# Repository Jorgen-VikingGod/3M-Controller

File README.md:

# 3M-Controller
3M-Controller = Multi Modular MIDI Controller

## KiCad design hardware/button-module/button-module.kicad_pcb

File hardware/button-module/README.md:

# BOM (for 1 board)
|QUANTITY|TYPE|DESCRIPTION|PACKAGE|Reference|
|--------|----|-----------|-------|---------|
|1|Microcontroller|ATXMEGA32A4U-AU|TQFP-44|U1|
|3|LevelShifter|74HCT245PW,118|TSSOP-20|U2, U3, U4|
|1|Zener Diode|MMSZ4684-TP 3.3V|SOD-123|D21|
|1|LDO|LD1117S33TR 3.3V|SOT-223|U5|
|20|Diode|1N4148W|SOD-123|D1 - D16|
|2|Resistor|220 Ohm|SMD-0805|R1, R2|
|1|Resistor|4.7 kOhm|SMD-0805|R5|
|1|Resistor|100 Ohm|SMD-0805|R3|
|7|Capacitor|6.3V 100 nF|SMD-0805|C1 - C7|

# BOM (for 10 boards, [arrow.com](https://www.arrow.com))
|PART|MANUFACTURER|QUANTITY|PRICE|PRICE TOTAL|DESCRIPTION|DETAILS|
|----|------------|--------|-----|-----------|-----------|-------|
|ATXMEGA32A4U-AU|Microchip Technology|10|2,4737|24,737|MCU 8-bit/16-bit XMEGA AVR RISC 32KB Flash 1.8V/2.5V/3.3V 44-Pin TQFP|https://www.arrow.com/en/products/atxmega32a4u-au/microchip-technology|
|74HCT245PW,118|Nexperia|30|0,1985|5,955|Bus XCVR Single 8-CH 3-ST 20-Pin TSSOP T/R|https://www.arrow.com/products/74hct245pw118/nexperia|
|MMSZ4684-TP|Micro Commercial Components|10|0,0708|0,708|Diode Zener Single 3.3V 5% 500mW 2-Pin SOD-123 T/R|https://www.arrow.com/products/mmsz4684-tp/micro-commercial-components|
|LD1117S33TR|STMicroelectronics|10|0,1713|1,713|LDO Regulator Pos 3.3V 1.3A 4-Pin(3+Tab) SOT-223 T/R|https://www.arrow.com/products/ld1117s33tr/stmicroelectronics|
|1N4148W|Good-Ark Semiconductor|200|0,0075|1,5|Diode Switching 75V 0.15A 2-Pin SOD-123|https://www.arrow.com/products/1n4148w/good-ark-semiconductor|
|NRC10J221TRF|NIC Components|20|0,0159|0,318|Res Thick Film 0805 220 Ohm 5% 0.125W(1/8W) ±200ppm/°C Pad SMD T/R|https://www.arrow.com/products/nrc10j221trf/nic-components|
|NRC10J101TRF|NIC Components|10|0,0141|0,141|Res Thick Film 0805 100 Ohm 5% 0.125W(1/8W) ±200ppm/°C Pad SMD T/R|https://www.arrow.com/products/nrc10j101trf/nic-components|
|RC0805JR-134K7L|Yageo|10|0,0175|0,175|Res Thick Film 0805 4.7K Ohm 5% 0.125W(1/8W) ±100ppm/°C Epoxy Pad SMD T/R|https://www.arrow.com/products/rc0805jr-134k7l/yageo|
|C0805C104K9RACTU|KEMET Corporation|70|0.0759|2.277|Cap Ceramic 0.1uF 6.3V X7R 10% Pad SMD 0805 125°C T/R|https://www.arrow.com/en/products/c0805c104k9ractu/kemet-corporation|

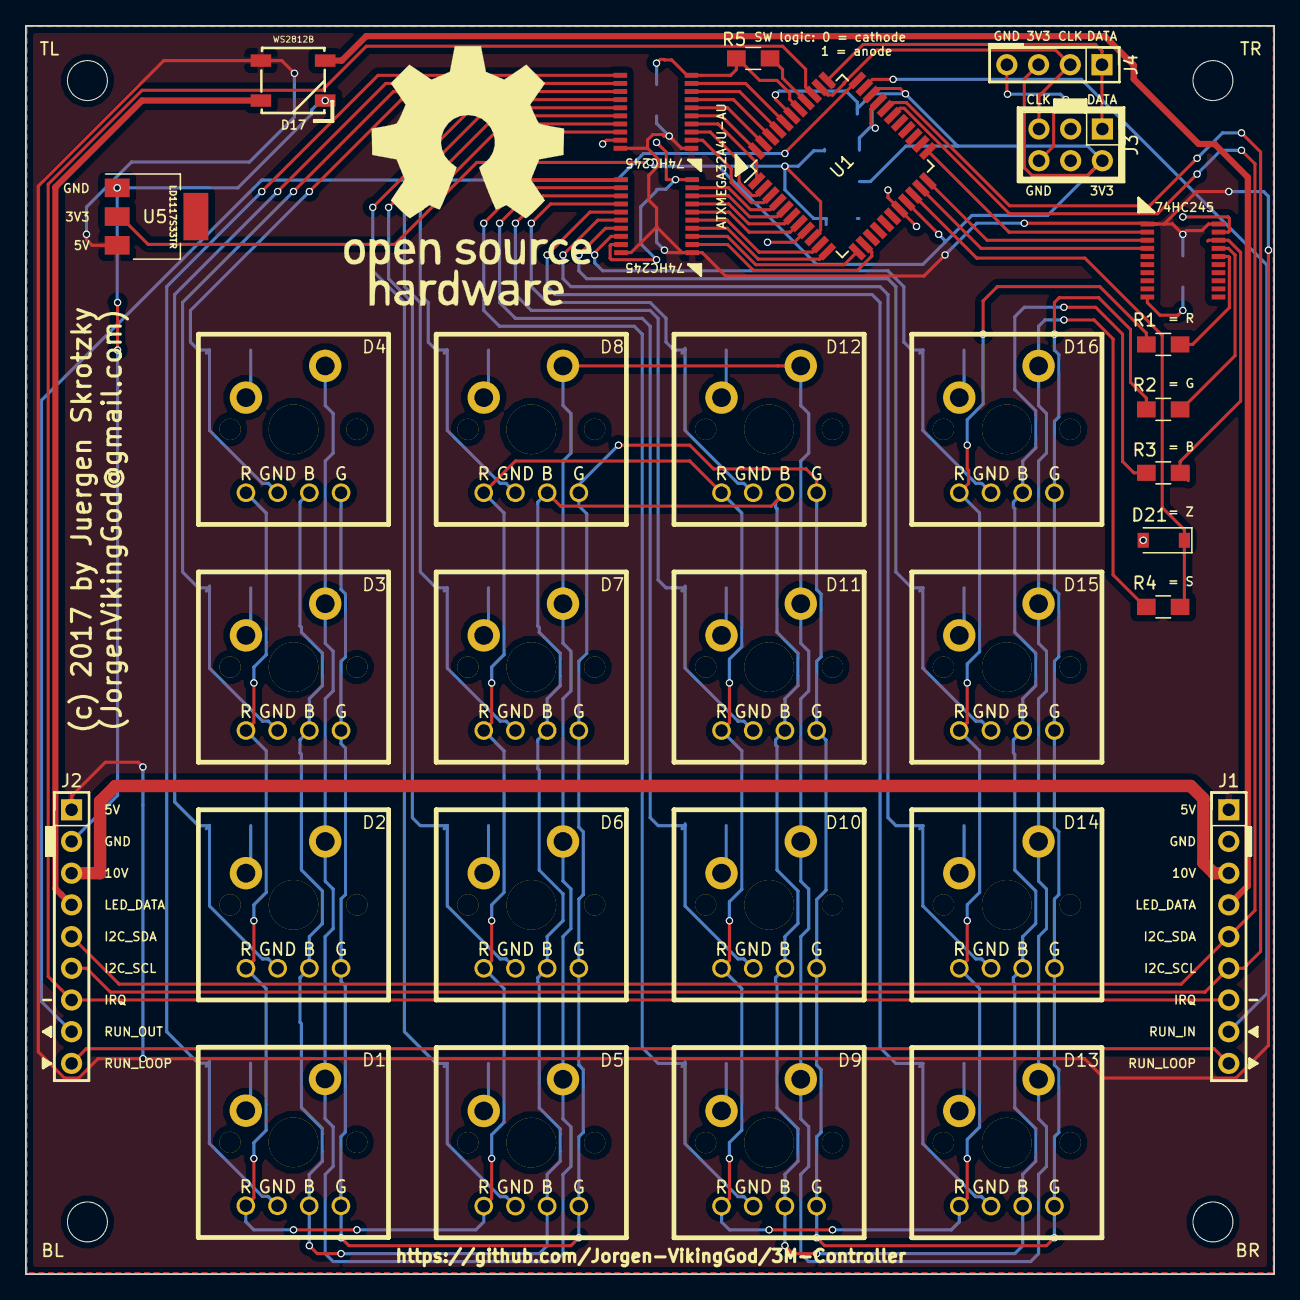
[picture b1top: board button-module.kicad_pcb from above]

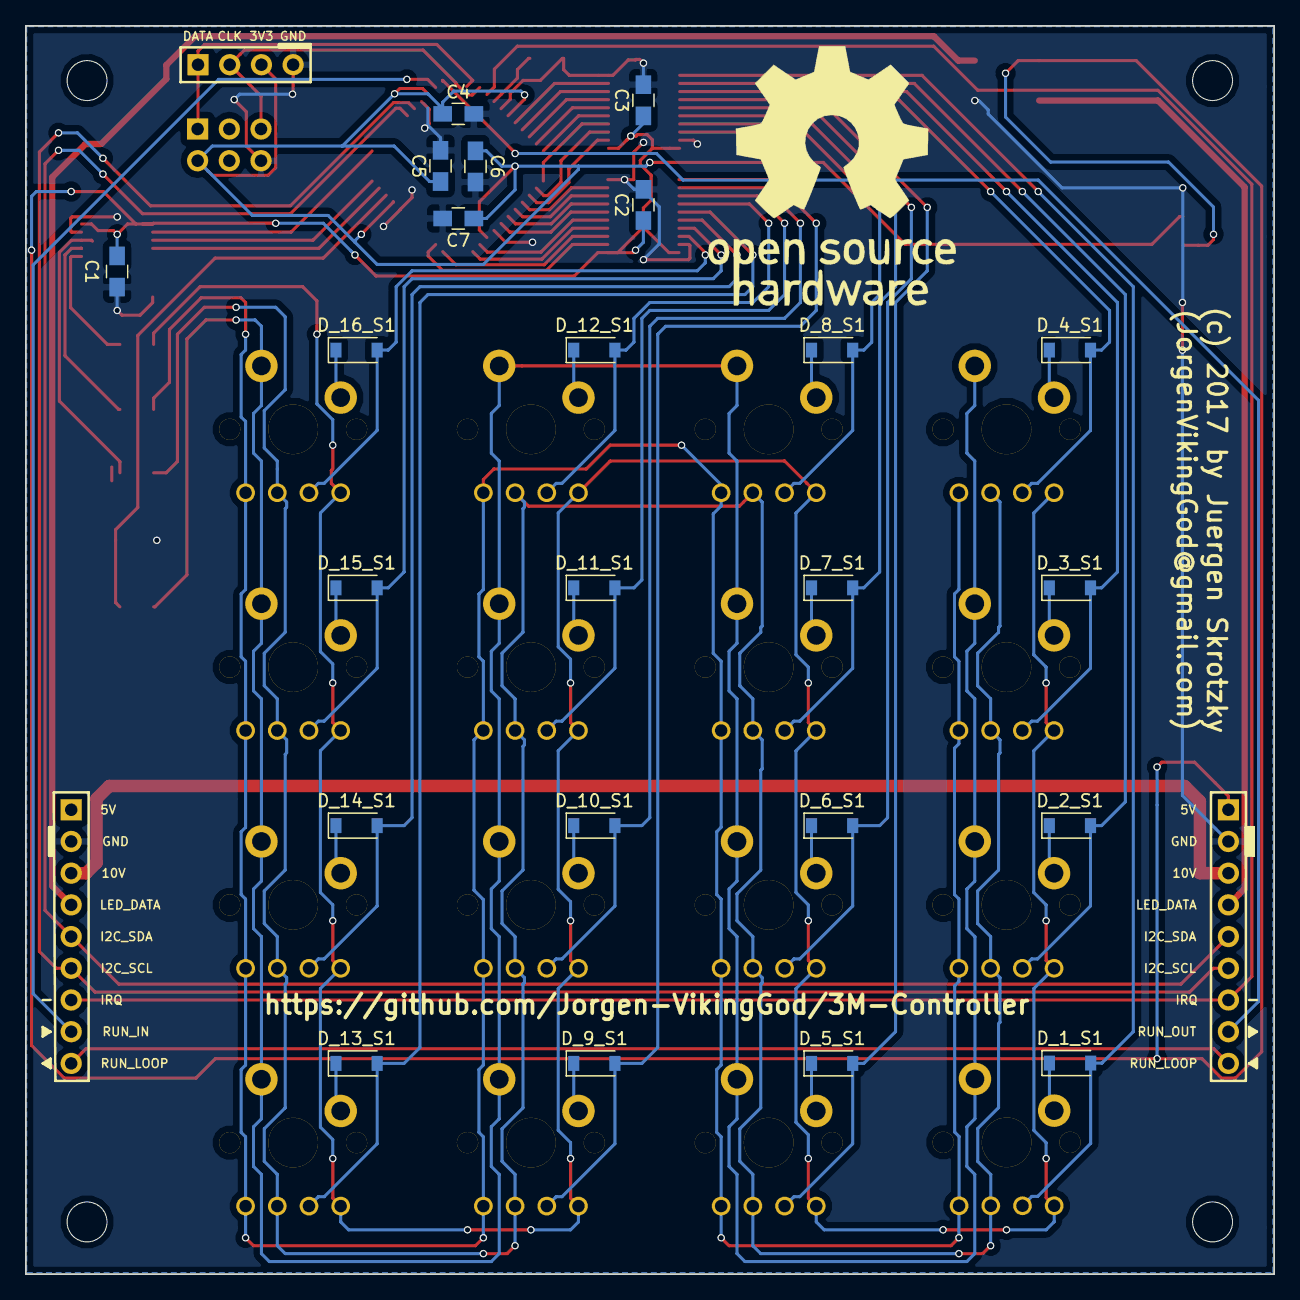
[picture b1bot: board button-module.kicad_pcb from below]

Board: 2 copper layers, 100.0 x 100.0 mm, 75 parts (23 on the bottom side), 74 nets.

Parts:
BL: MountingHole_3.2mm_M3
BR: MountingHole_3.2mm_M3
C1, C2, C3, C4, C5, C6, C7: 100n; C_0805_HandSoldering
D1: LED1; RGB
D2: LED2; RGB
D3: LED3; RGB
D4: LED4; RGB
D5: LED5; RGB
D6: LED6; RGB
D7: LED7; RGB
D8: LED8; RGB
D9: LED9; RGB
D10: LED10; RGB
D11: LED11; RGB
D12: LED12; RGB
D13: LED13; RGB
D14: LED14; RGB
D15: LED15; RGB
D16: LED16; RGB
D17: WS2812B
D21: D_Zener; D_SOD-123
D_1_S1, D_2_S1, D_3_S1, D_4_S1, D_5_S1, D_6_S1, D_7_S1, D_8_S1, D_9_S1, D_10_S1, D_11_S1, D_12_S1, D_13_S1, D_14_S1, D_15_S1, D_16_S1: D; D_SOD-123
J1, J2: CONN_01X09; Pin_Header_Straight_1x09_Pitch2.54mm
J3: CONN_02X03; Pin_Header_Straight_2x03_Pitch2.54mm
J4: CONN_01X04; Pin_Header_Straight_1x04_Pitch2.54mm
R1, R2, R3: 4K; R_0805_HandSoldering
R4, R5: R; R_0805_HandSoldering
SW1, SW2, SW3, SW4, SW5, SW6, SW7, SW8, SW9, SW10, SW11, SW12, SW13, SW14, SW15, SW16: SW_PUSH; MX1A
TL: MountingHole_3.2mm_M3
TR: MountingHole_3.2mm_M3
U1: ATXMEGA32A4U-AU; TQFP-44_10x10mm_Pitch0.8mm
U2, U3, U4: 74HC245; TSSOP20
U5: LD1117S33TR; SOT-223

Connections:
+3V3: C4.1, C5.1, C6.1, C7.1, J3.2, J4.3, U1.9, U1.19, U1.31, U1.39, U5.2
+12V: J1.3, J2.3
/C_1_R: R1.1, U4.16
/C_2_R: R2.1, U4.17
/C_3_R: R3.1, U4.18
COLOR_1_3V3: U1.21, U4.4
COLOR_1_5V: D1.2, D2.2, D3.2, D4.2, D5.2, D6.2, D7.2, D8.2, D9.2, D10.2, D11.2, D12.2, D13.2, D14.2, D15.2, D16.2, R1.2
COLOR_2_3V3: U1.22, U4.3
COLOR_2_5V: D1.3, D2.3, D3.3, D4.3, D5.3, D6.3, D7.3, D8.3, D9.3, D10.3, D11.3, D12.3, D13.3, D14.3, D15.3, D16.3, R2.2
COLOR_3_3V3: U1.23, U4.2
COLOR_3_5V: D1.4, D2.4, D3.4, D4.4, D5.4, D6.4, D7.4, D8.4, D9.4, D10.4, D11.4, D12.4, D13.4, D14.4, D15.4, D16.4, R3.2
GND: C1.2, C2.2, C3.2, C4.2, C5.2, C6.2, C7.2, D17.3, D21.2, J1.2, J2.2, J3.6, J4.4, R5.1, U1.8, U1.18, U1.30, U1.38, U2.10, U2.19, U3.10, U3.19, U4.10, U4.19, U5.1
I2C_SCL: J1.6, J2.6, U1.29
I2C_SDA: J1.5, J2.5, U1.28
IRQ_OUT: J1.7, J2.7, U1.36
LED_DATA_IN: D17.4, J1.4
LED_DATA_OUT: D17.2, J2.4
MUX_1_3V3: U1.40, U2.9
MUX_1_5V: D1.1, D_1_S1.2, U2.11
MUX_2_3V3: U1.41, U2.8
MUX_2_5V: D2.1, D_2_S1.2, U2.12
MUX_3_3V3: U1.42, U2.7
MUX_3_5V: D3.1, D_3_S1.2, U2.13
MUX_4_3V3: U1.43, U2.6
MUX_4_5V: D4.1, D_4_S1.2, U2.14
MUX_5_3V3: U1.44, U2.5
MUX_5_5V: D5.1, D_5_S1.2, U2.15
MUX_6_3V3: U1.1, U2.4
MUX_6_5V: D6.1, D_6_S1.2, U2.16
MUX_7_3V3: U1.2, U2.3
MUX_7_5V: D7.1, D_7_S1.2, U2.17
MUX_8_3V3: U1.3, U2.2
MUX_8_5V: D8.1, D_8_S1.2, U2.18
MUX_9_3V3: U1.4, U3.9
MUX_9_5V: D9.1, D_9_S1.2, U3.11
MUX_10_3V3: U1.5, U3.8
MUX_10_5V: D10.1, D_10_S1.2, U3.12
MUX_11_3V3: U1.6, U3.7
MUX_11_5V: D11.1, D_11_S1.2, U3.13
MUX_12_3V3: U1.7, U3.6
MUX_12_5V: D12.1, D_12_S1.2, U3.14
MUX_13_3V3: U1.10, U3.5
MUX_13_5V: D13.1, D_13_S1.2, U3.15
MUX_14_3V3: U1.11, U3.4
MUX_14_5V: D14.1, D_14_S1.2, U3.16
MUX_15_3V3: U1.12, U3.3
MUX_15_5V: D15.1, D_15_S1.2, U3.17
MUX_16_3V3: U1.13, U3.2
MUX_16_5V: D16.1, D_16_S1.2, U3.18
unnamed: D_1_S1.1, SW1.1
unnamed: D_2_S1.1, SW2.1
unnamed: D_3_S1.1, SW3.1
unnamed: D_4_S1.1, SW4.1
unnamed: D_5_S1.1, SW5.1
unnamed: D_6_S1.1, SW6.1
unnamed: D_7_S1.1, SW7.1
unnamed: D_8_S1.1, SW8.1
unnamed: D_9_S1.1, SW9.1
unnamed: D_10_S1.1, SW10.1
unnamed: D_11_S1.1, SW11.1
unnamed: D_12_S1.1, SW12.1
unnamed: D_13_S1.1, SW13.1
unnamed: D_14_S1.1, SW14.1
unnamed: D_15_S1.1, SW15.1
unnamed: D_16_S1.1, SW16.1
unnamed: R5.2, U1.37
PDI_CLOCK: J3.5, J4.2, U1.35
PDI_DATA: J3.1, J4.1, U1.34
RUN_IN: J1.8, U1.32
RUN_LOOP: J1.9, J2.9
RUN_OUT: J2.8, U1.33
SWITCH_IN: R4.2, SW1.2, SW2.2, SW3.2, SW4.2, SW5.2, SW6.2, SW7.2, SW8.2, SW9.2, SW10.2, SW11.2, SW12.2, SW13.2, SW14.2, SW15.2, SW16.2
SW_Z_IN: D21.1, R4.1, U1.20
VCC: C1.1, C2.1, C3.1, D17.1, J1.1, J2.1, U2.1, U2.20, U3.1, U3.20, U4.1, U4.20, U5.3

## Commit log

2017-04-23 Rename hardware/main/README.md to hardware/main-controller/README.md
2017-04-23 first test code
2017-04-25 change display lib to support RGB displays
2017-04-25 add initial kicad project
2017-04-25 XMEGA + switches + RGB LEDs
2017-04-25 add pdf of first schematic
2017-04-25 add copyright
2017-04-25 finish schematic + initial pcb
2017-04-25 update schematic pdf
2017-04-26 rename pads + pcb layout
2017-04-26 first test route
2017-04-26 reset pub and start new routing
2017-04-26 move diode to layer 2 and rearrange buttons
2017-04-30 add zener diode + continue routing
2017-05-03 continue routing (SDA,SCL)
2017-05-04 test route
2017-05-05 test pcb route 0.5
2017-05-05 pcb without warnings
2017-05-05 place small mounting holes to stabilise board
2017-05-10 finish pcb with additional PCM JTAG header
2017-05-14 final design
2017-05-15 final pub design and gerber files
2017-05-15 add schematic pdf and pcb front/back image
2017-05-15 add 3d images of pub board
2017-05-22 update BOM
2017-05-26 update c from 100u to 100n
2017-06-08 change silk screen to avoid wrong placing of parts
2017-06-08 modify berbers and images based on pub silk screen changes
2017-06-11 modify sketch and update pub (not working yet)
2017-06-11 esp32 version only
2017-06-11 merged esp32 version
2017-06-11 Revert "merged esp32 version"
    This reverts commit c84f3c4945b4e72ce8df394fc8620ed180273c76.
2017-06-11 esp32 only
2017-06-11 update 100nF cap instead of 22 uF
2017-07-07 update PCB and Schematics
    bugfix wrong pin mapping of LevelShifter and rearrange components
    (change pin headers from 1.27mm to 2.54mm)
2017-07-10 update 3d preview images
2017-07-10 add add. Cs and MCU link
2017-07-24 update silk screen
2017-07-24 Revert "update silk screen"
    This reverts commit 59520df7f3309911bfd52b2003e2d7e46adb0319.
2017-07-24 Revert "Revert "update silk screen""
    This reverts commit b984289455377b0220fd624303609a1432511432.
2017-08-09 remove bias from pads
2018-01-05 update gerber and zip file

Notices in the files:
hardware/button-module/button-module.kicad_pcb:
(c) 2017 by Juergen Skrotzky
